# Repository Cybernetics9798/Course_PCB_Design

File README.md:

# Course_PCB_Design
PCB designs for 2EI4 and 3EJ4

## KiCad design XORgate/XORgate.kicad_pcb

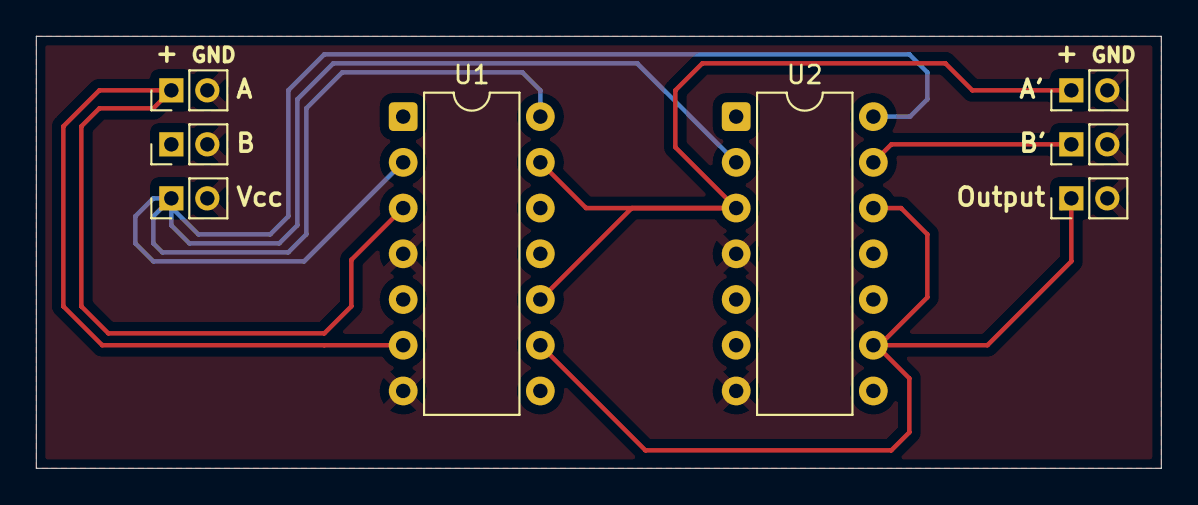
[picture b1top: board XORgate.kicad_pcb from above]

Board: 4 copper layers, 62.5 x 24.0 mm, 8 parts (0 on the bottom side), 9 nets.

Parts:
J1, J2, J3, J4, J5, J6: Conn_01x02_Pin; PinHeader_1x02_P2.00mm_Vertical
U1, U2: DIP-14_W7.62mm

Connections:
A: J1.1, U1.3 (G), U1.6 (G)
A': J5.1, U1.8 (D), U1.10 (G), U1.13 (S), U2.3 (G)
B: J2.1, U2.6 (G), U2.10 (G)
B': J6.1, U2.8 (D), U2.13 (S)
GND: J1.2, J2.2, J3.2, J4.2, J5.2, J6.2, U1.4 (S), U1.7 (S), U2.4 (S), U2.7 (S)
unnamed: J3.1, U1.9 (D), U1.12 (D), U2.9 (D), U2.12 (D)
unnamed: U1.1 (S), U1.11 (S)
unnamed: U2.1 (S), U2.11 (S)
Vcc: J4.1, U1.2 (D), U1.14 (D), U2.2 (D), U2.14 (D)

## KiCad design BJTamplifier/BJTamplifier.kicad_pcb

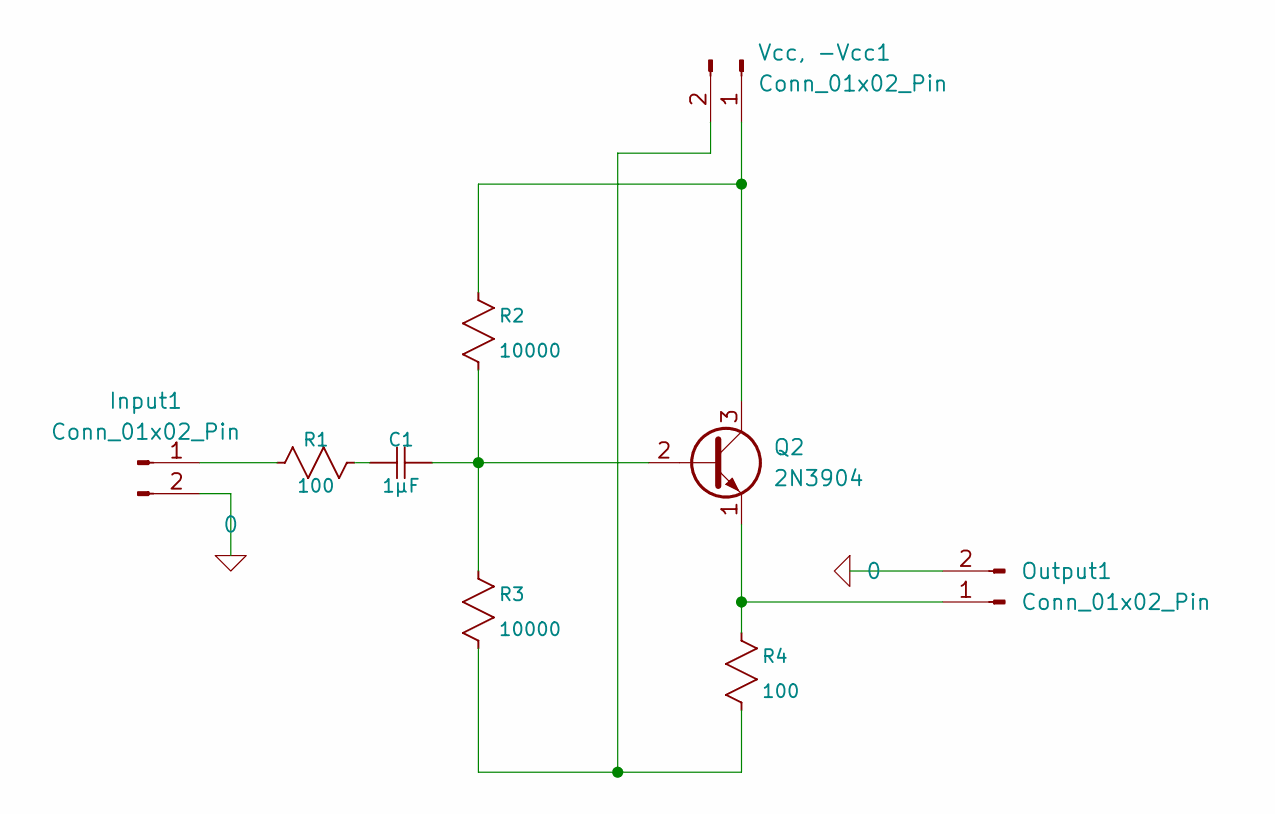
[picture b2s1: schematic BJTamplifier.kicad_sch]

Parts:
C1: 1µF; C_Disc_D3.4mm_W2.1mm_P2.50mm
Input1: Conn_01x02_Pin; PinHeader_1x02_P2.00mm_Vertical
Output1: Conn_01x02_Pin; PinHeader_1x02_P2.00mm_Vertical
Q2: 2N3904; TO-92_Inline
R1, R4: 100; R_Axial_DIN0207_L6.3mm_D2.5mm_P10.16mm_Horizontal
R2, R3: 10000; R_Axial_DIN0207_L6.3mm_D2.5mm_P10.16mm_Horizontal
Vcc, -Vcc1: Conn_01x02_Pin; PinHeader_1x02_P2.00mm_Vertical

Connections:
0: Input1.2, Output1.2
unnamed: C1.2, R1.1
unnamed: Input1.1, R1.2
unnamed: Output1.1, Q2.1 (E), R4.1
unnamed: C1.1, Q2.2 (B), R2.2, R3.1
unnamed: Q2.3 (C), R2.1, Vcc, -Vcc1.1
unnamed: R3.2, R4.2, Vcc, -Vcc1.2

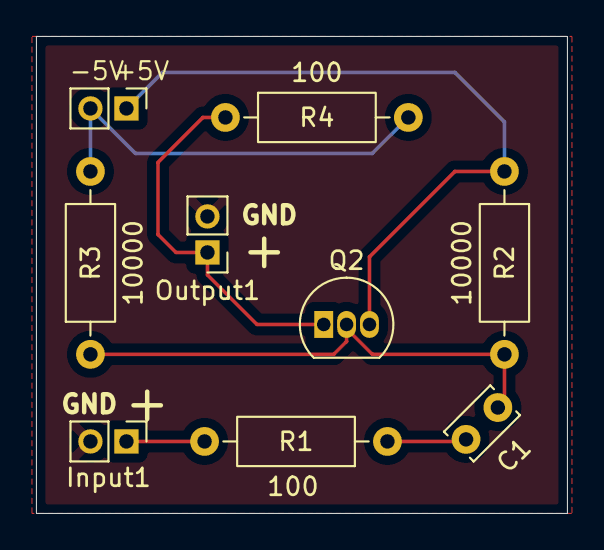
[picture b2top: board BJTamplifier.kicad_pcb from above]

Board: 2 copper layers, 29.5 x 26.5 mm, 9 parts (0 on the bottom side), 7 nets.

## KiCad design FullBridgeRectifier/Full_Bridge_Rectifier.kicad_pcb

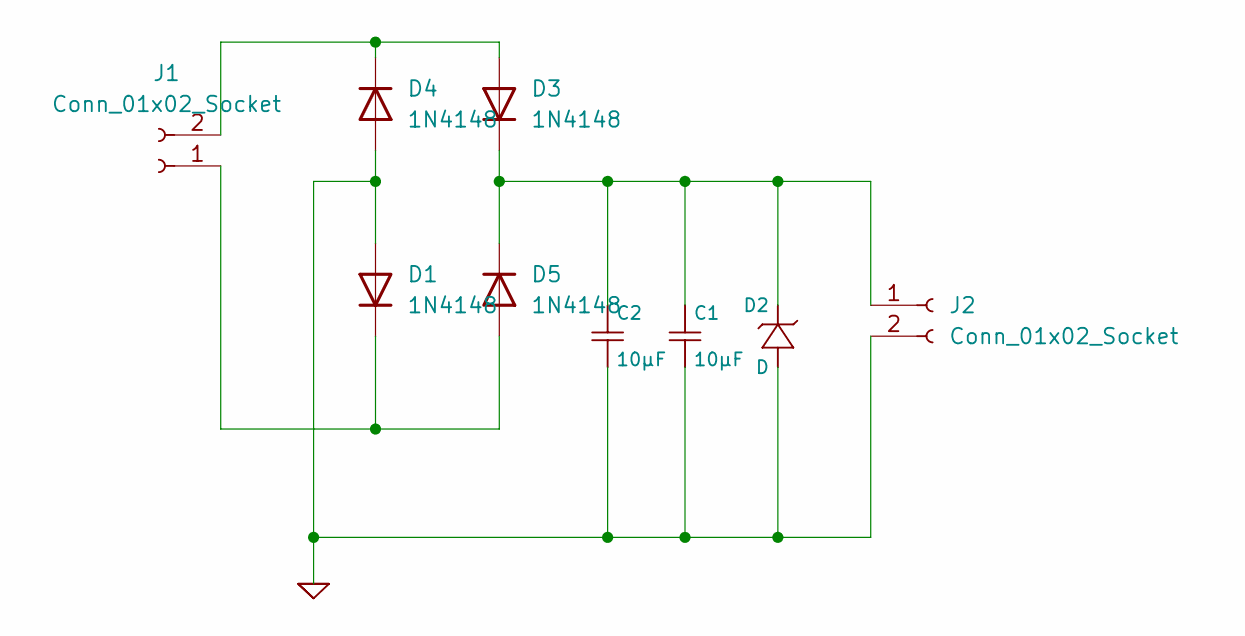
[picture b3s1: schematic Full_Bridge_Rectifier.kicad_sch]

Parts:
C1, C2: 10µF; CP_Radial_D4.0mm_P2.00mm
D1, D3, D4, D5: 1N4148; D_DO-35_SOD27_P7.62mm_Horizontal
D2: D; D_DO-35_SOD27_P7.62mm_Horizontal
J1, J2: Conn_01x02_Socket; PinSocket_1x02_P2.00mm_Vertical

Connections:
0: C1.2, C2.2, D1.2 (A), D2.1 (+), D4.2 (A), J2.2
unnamed: D1.1 (K), D5.2 (A), J1.1
unnamed: C1.1, C2.1, D2.2 (-), D3.1 (K), D5.1 (K), J2.1
unnamed: D3.2 (A), D4.1 (K), J1.2

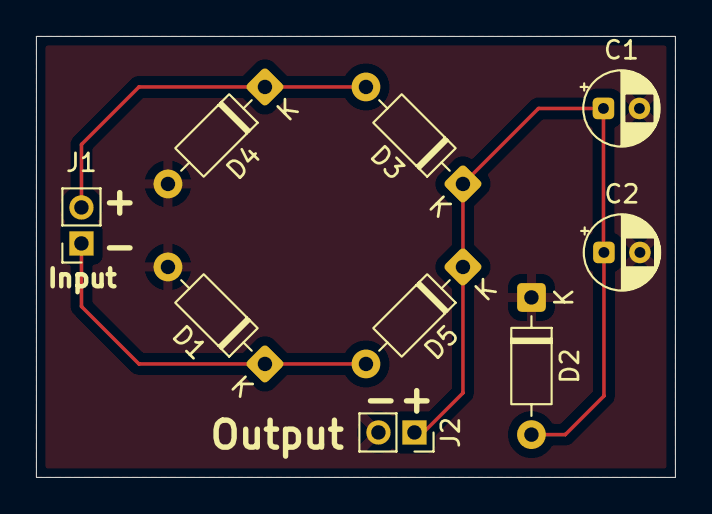
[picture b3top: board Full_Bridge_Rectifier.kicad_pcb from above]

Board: 2 copper layers, 35.5 x 24.5 mm, 9 parts (0 on the bottom side), 4 nets.

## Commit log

2025-12-28 2EI4 lab1 complete
2025-12-31 XOR gate
